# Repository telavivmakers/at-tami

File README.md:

ATtami עָלֵקדוּאִינו
=================

fork of littlewire AVR based Vusb dev board and various other efforts around the ATtiny85 <br>
more at [docs.telavivmakers.space/attami](https://docs.telavivmakers.space/attami)<br>

Schematics
===

board layout
===

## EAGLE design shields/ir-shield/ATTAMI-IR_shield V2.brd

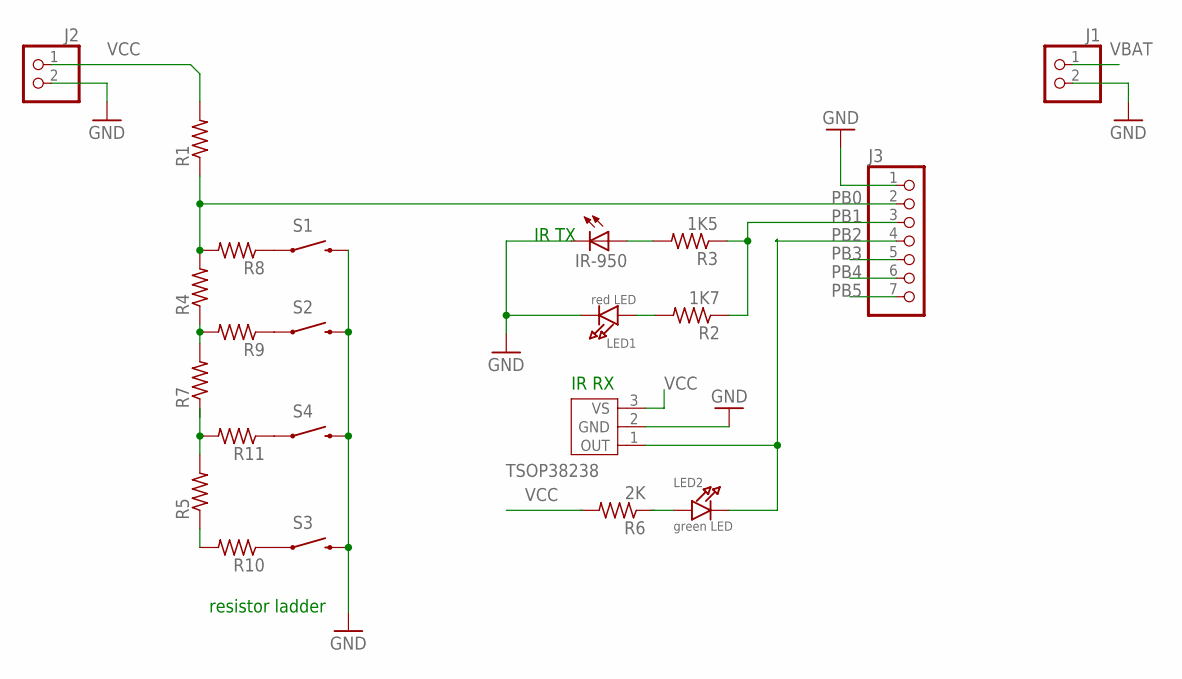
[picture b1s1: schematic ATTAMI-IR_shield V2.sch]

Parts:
IR-950: LEDIRL80A; IRL80A
J1, J2: HEADER-1X2ROUND; 1X02_ROUND
J3: HEADER-1X7ROUND; 1X07_ROUND
LED1: red LED; CHIPLED_0805
LED2: green LED; CHIPLED_0805
R1, R4, R5, R7, R8, R9, R10, R11: R-US_M0805; M0805
R2: 1K7; M0805
R3: 1K5; M0805
R6: 2K; M0805
S1, S2, S3, S4: SWITCH-MOMENTARY-2-SMD-1101NE; TACTILE-SWITCH-1101NE
TSOP38238: TSOP382; 3P-2.54-4.8X5X6.95H

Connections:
GND: IR-950.K (C), J1.2, J2.2, J3.1, LED1.C, S1.P$2 (2), S2.P$2 (2), S3.P$2 (2), S4.P$2 (2), TSOP38238.2 (GND)
unnamed: R9.1, S2.P$1 (1)
unnamed: R8.1, S1.P$1 (1)
unnamed: R10.1, S3.P$1 (1)
unnamed: LED1.A, R2.2
unnamed: R5.2, R11.2
unnamed: R4.1, R7.2, R9.2
unnamed: R5.1, R10.2
unnamed: IR-950.A, R3.2
unnamed: R11.1, S4.P$1 (1)
PB0: J3.2, R1.1, R4.2, R8.2
PB1: J3.3, R2.1, R3.1
PB2: J3.4, LED2.C, TSOP38238.1 (OUT)
PB3: J3.5
PB4: J3.6
PB5: J3.7
VBAT: J1.1
VCC: J2.1, R1.2, TSOP38238.3 (VS)

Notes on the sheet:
resistor ladder
IR TX
IR RX

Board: 2 copper layers, 22 parts (0 on the bottom side), 14 nets, no tracks yet.

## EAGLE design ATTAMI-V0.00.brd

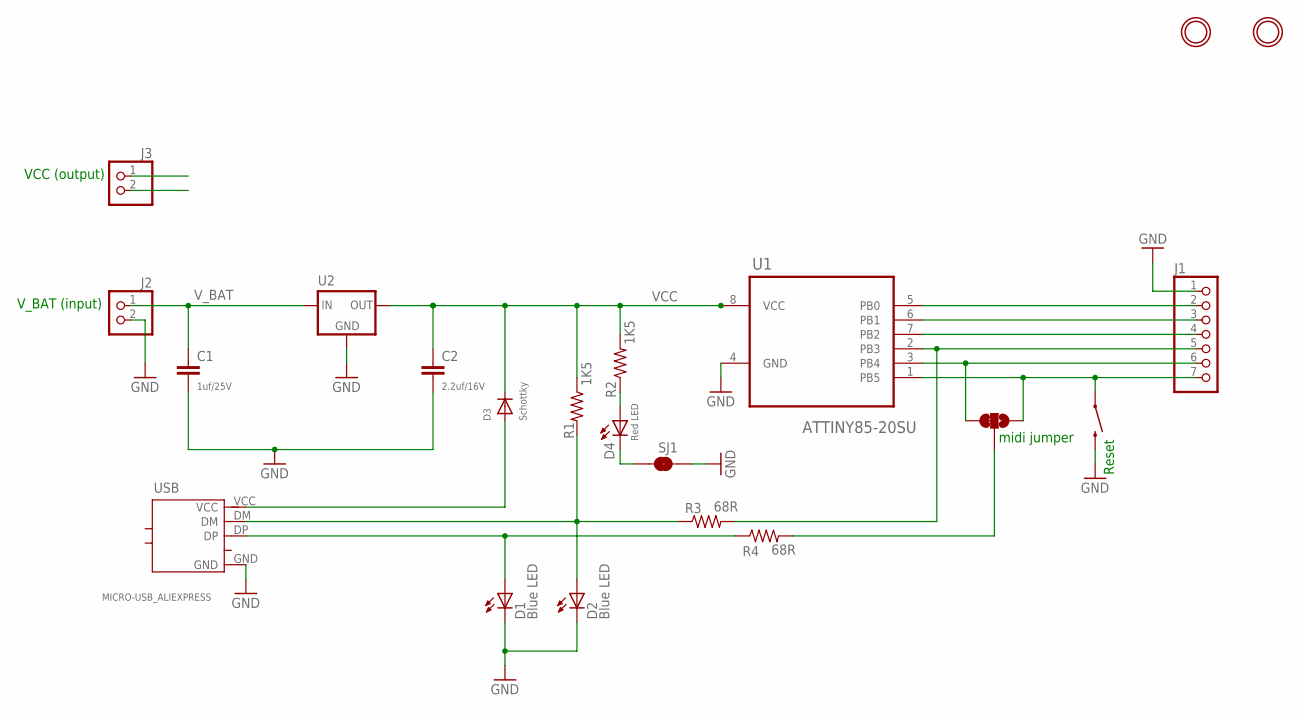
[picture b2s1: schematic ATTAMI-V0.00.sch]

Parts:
C1: 1uf/25V; 0805
C2: 2.2uf/16V; 0805
D1, D2: Blue LED; LED-805
D3: Schottky; SOD-323
D4: Red LED; LED-805
J1: HEADER-1X7ROUND; 1X07_ROUND
J2, J3: HEADER-1X2ROUND; 1X02_ROUND
MIDI: JUMPER-PAD-3-2OF3_NC_BY_TRACE_SMALL; PAD-JUMPER-3-2OF3_NC_BY_TRACE_YES_SILK_FULL_BOX
R1, R2: 1K5; 0805
R3, R4: 68R; 0805
S1: SWITCH-MOMENTARY-2-SMD-1101NE; TACTILE-SWITCH-1101NE
SJ1: JUMPER-PAD-2-NC_BY_TRACE; PAD-JUMPER-2-NC_BY_TRACE_YES_SILK
U1: ATTINY85-20SU; SOIC127P798X216-8N
U2: XXX1117SOT-232; SOT-223
U$1, U$2: MOUNTINGHOLE2.0; MOUNTINGHOLE_2.0_PLATED
USB: MICRO-USB_ALIEXPRESS; USB-MICRO-ALIEXPRESS

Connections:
GND: C1.2, C2.2, D1.C, D2.C, J1.1, J2.2, J3.2, S1.P$2 (2), SJ1.1, U1.4 (GND), U2.1 (GND), USB.GND
unnamed: MIDI.2, R4.2
unnamed: D1.A, R4.1, USB.DP
unnamed: D2.A, R1.2, R3.1, USB.DM
unnamed: D4.A, R2.1
unnamed: D4.C, SJ1.2
PB0: J1.2, U1.5 (PB0)
PB1: J1.3, U1.6 (PB1)
PB2: J1.4, U1.7 (PB2)
PB3: J1.5, R3.2, U1.2 (PB3)
PB4: J1.6, MIDI.3, U1.3 (PB4)
PB5: J1.7, MIDI.1, S1.P$1 (1), U1.1 (PB5)
V-BUS: D3.AQ (A), USB.VCC
VCC: C2.1, D3.CQ (C), J3.1, R1.1, R2.2, U1.8 (VCC), U2.2 (OUT), U2.4 (OUT)
V_BAT: C1.1, J2.1, U2.3 (IN)

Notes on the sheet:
VCC (output)
V_BAT (input)
Reset
midi jumper

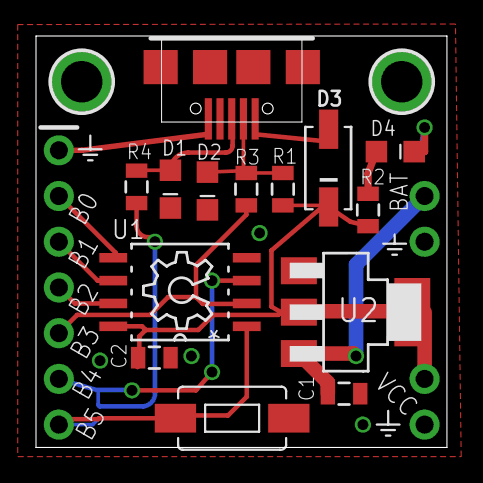
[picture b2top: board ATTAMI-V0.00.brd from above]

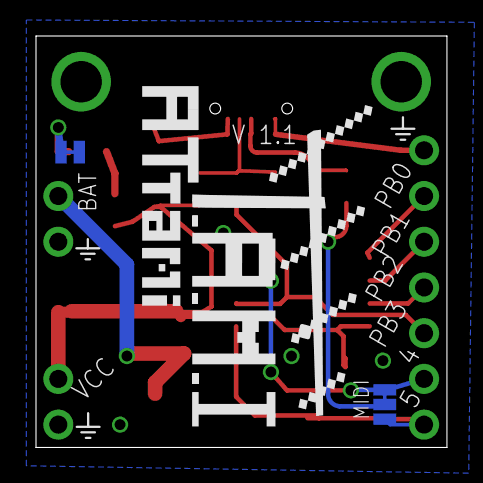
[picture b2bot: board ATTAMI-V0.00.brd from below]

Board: 2 copper layers, 22.8 x 22.9 mm, 22 parts (2 on the bottom side), 15 nets.

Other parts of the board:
U$3: OSHW_6X150_NOTEXT

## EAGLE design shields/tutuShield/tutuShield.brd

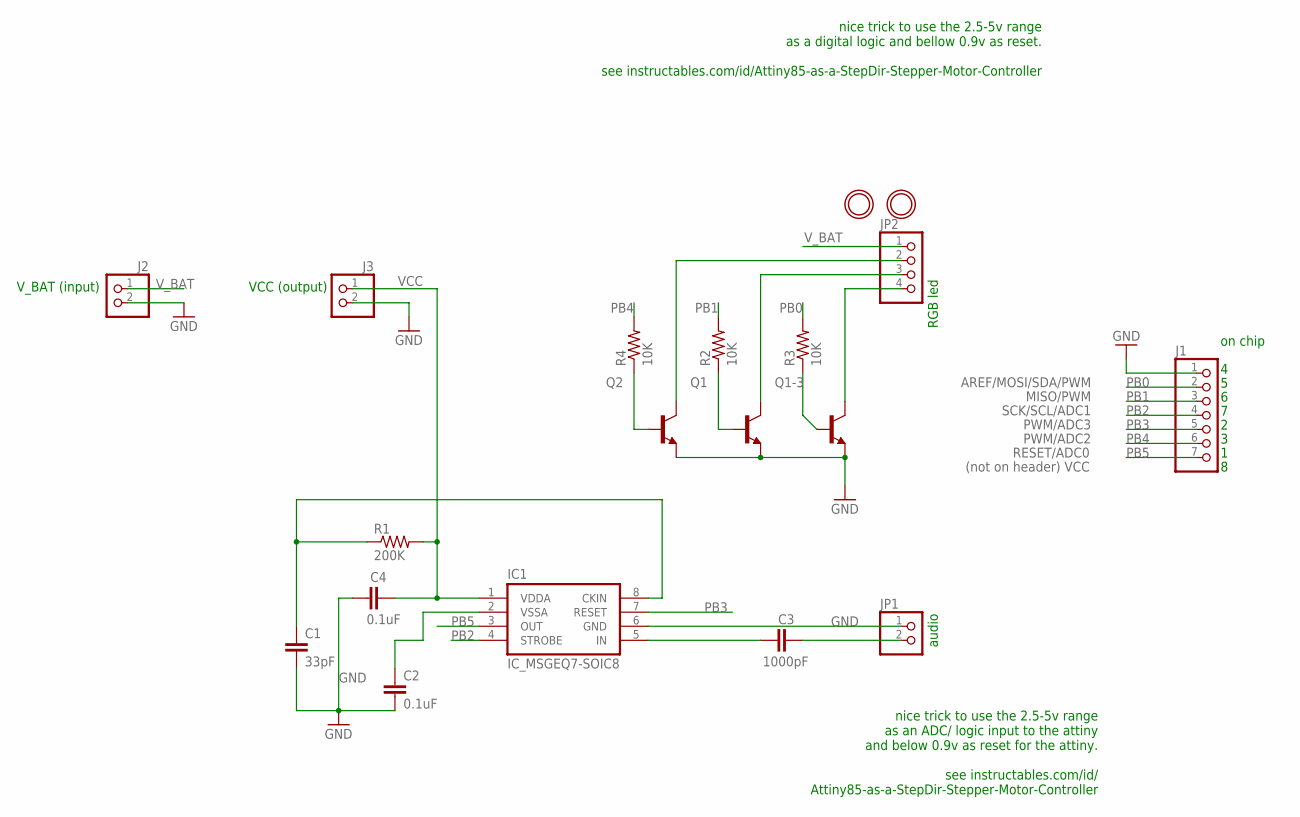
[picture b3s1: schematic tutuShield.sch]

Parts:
C1: 33pF; 0805
C2, C4: 0.1uF; 0805
C3: 1000pF; 0805
IC1: IC_MSGEQ7-SOIC8; SOIC-8
J1: HEADER-1X7ROUND; 1X07_ROUND
J2, J3: HEADER-1X2ROUND; 1X02_ROUND
JP1: HEADER-1X2ROUND; 1X02_ROUND
JP2: HEADER-1X4ROUND; 1X04_ROUND
Q1, Q1-3, Q2: TRANSISTOR_BJT_NPN-SOT-23-BEC; SOT-23
R1: 200K; 0805
R2, R3, R4: 10K; 0805
U$1, U$2: MOUNTINGHOLE2.0; MOUNTINGHOLE_2.0_PLATED

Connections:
CKIN: C1.1, IC1.8 (CKIN), R1.1
GND: C1.2, C2.2, C4.1, IC1.6 (GND), J1.1, J2.2, J3.2, JP1.1, Q1.2 (E), Q1-3.2 (E), Q2.2 (E)
IN: C3.1, IC1.5 (IN)
unnamed: C3.2, JP1.2
unnamed: Q1-3.1 (B), R3.1
unnamed: JP2.2, Q2.3 (C)
unnamed: C2.1, IC1.2 (VSSA)
unnamed: Q1.1 (B), R2.1
unnamed: Q2.1 (B), R4.1
unnamed: JP2.4, Q1-3.3 (C)
unnamed: JP2.3, Q1.3 (C)
PB0: J1.2, R3.2
PB1: J1.3, R2.2
PB2: IC1.4 (STROBE), J1.4
PB3: IC1.7 (RESET), J1.5
PB4: J1.6, R4.2
PB5: IC1.3 (OUT), J1.7
VCC: C4.2, IC1.1 (VDDA), J3.1, R1.2
V_BAT: J2.1, JP2.1

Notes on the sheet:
VCC (output)
V_BAT (input)
RESET/ADC0
PWM/ADC3
SCK/SCL/ADC1
PWM/ADC2
MISO/PWM
AREF/MOSI/SDA/PWM
on chip 4 5 6 7 2 3 1 8
(not on header) VCC
nice trick to use the 2.5-5v range as a digital logic and bellow 0.9v as reset. see instructables.com/id/Attiny85-as-a-StepDir-Stepper-Motor-Controller
nice trick to use the 2.5-5v range as an ADC/ logic input to the attiny and below 0.9v as reset for the attiny. see instructables.com/id/ Attiny85-as-a-StepDir-Stepper-Motor-Controller
audio
RGB led

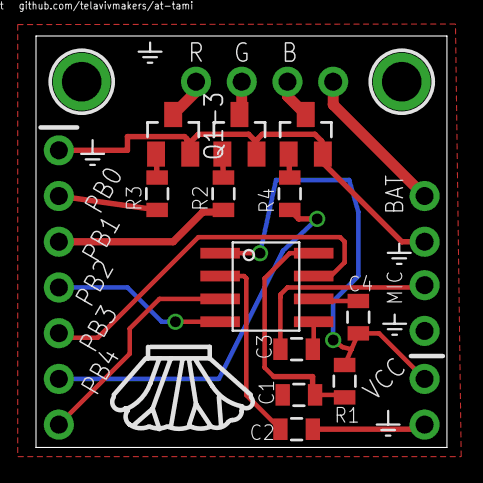
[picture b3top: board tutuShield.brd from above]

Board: 2 copper layers, 22.8 x 22.9 mm, 19 parts (0 on the bottom side), 19 nets.

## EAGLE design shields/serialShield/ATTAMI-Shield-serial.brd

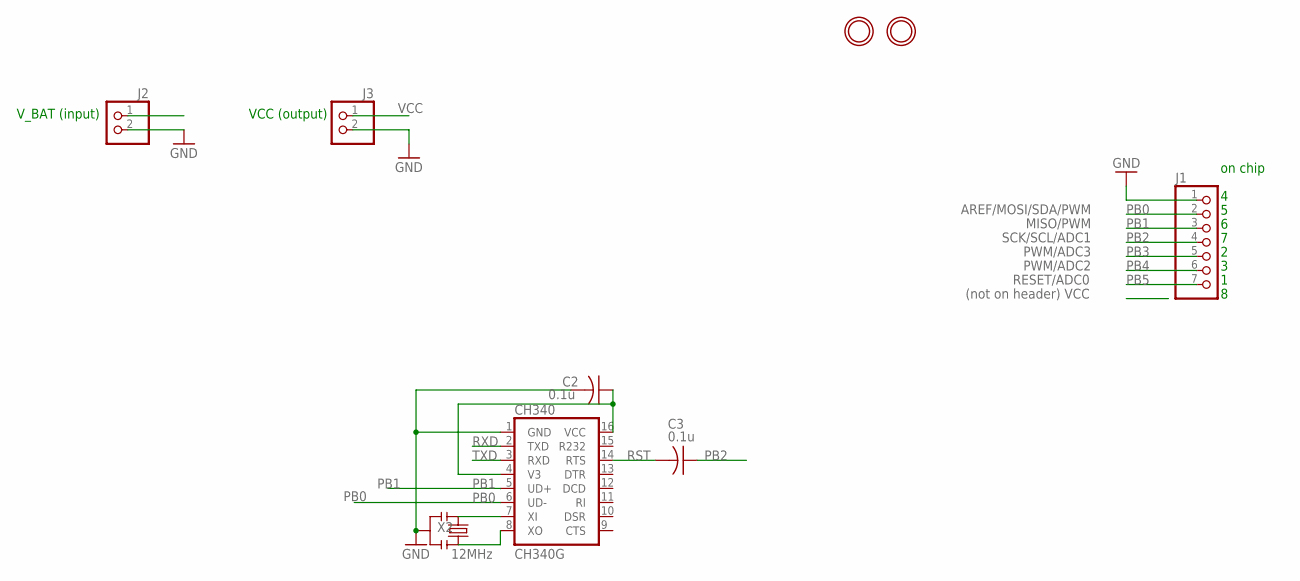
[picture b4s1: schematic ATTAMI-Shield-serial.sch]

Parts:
C2, C3: 0.1u; C0603
CH340: CH340G; SO16
J1: HEADER-1X7ROUND; 1X07_ROUND
J2, J3: HEADER-1X2ROUND; 1X02_ROUND
U$1, U$2: MOUNTINGHOLE2.0; MOUNTINGHOLE_2.0_PLATED
X2: 12MHz; RESONATOR-SMD

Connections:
GND: C2.2, CH340.1 (GND), J1.1, J2.2, J3.2, X2.2
unnamed: CH340.7 (XI), X2.1
unnamed: CH340.8 (XO), X2.3
PB0: CH340.6 (UD-), J1.2
PB1: CH340.5 (UD+), J1.3
PB2: C3.1, J1.4
PB3: J1.5
PB4: J1.6
PB5: J1.7
RST: C3.2, CH340.14 (RTS)
RXD: CH340.2 (TXD)
TXD: CH340.3 (RXD)
VCC: C2.1, CH340.4 (V3), CH340.16 (VCC), J3.1

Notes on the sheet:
VCC (output)
V_BAT (input)
RESET/ADC0
PWM/ADC3
SCK/SCL/ADC1
PWM/ADC2
MISO/PWM
AREF/MOSI/SDA/PWM
on chip 4 5 6 7 2 3 1 8
(not on header) VCC

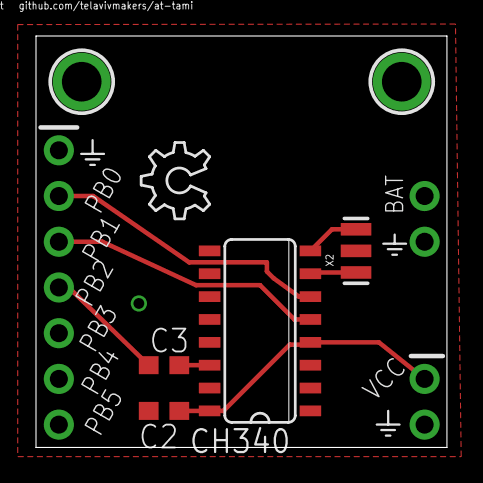
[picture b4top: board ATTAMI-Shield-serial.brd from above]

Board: 2 copper layers, 22.8 x 22.9 mm, 10 parts (0 on the bottom side), 8 nets.

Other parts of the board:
U$3: OSHW_6X150_NOTEXT

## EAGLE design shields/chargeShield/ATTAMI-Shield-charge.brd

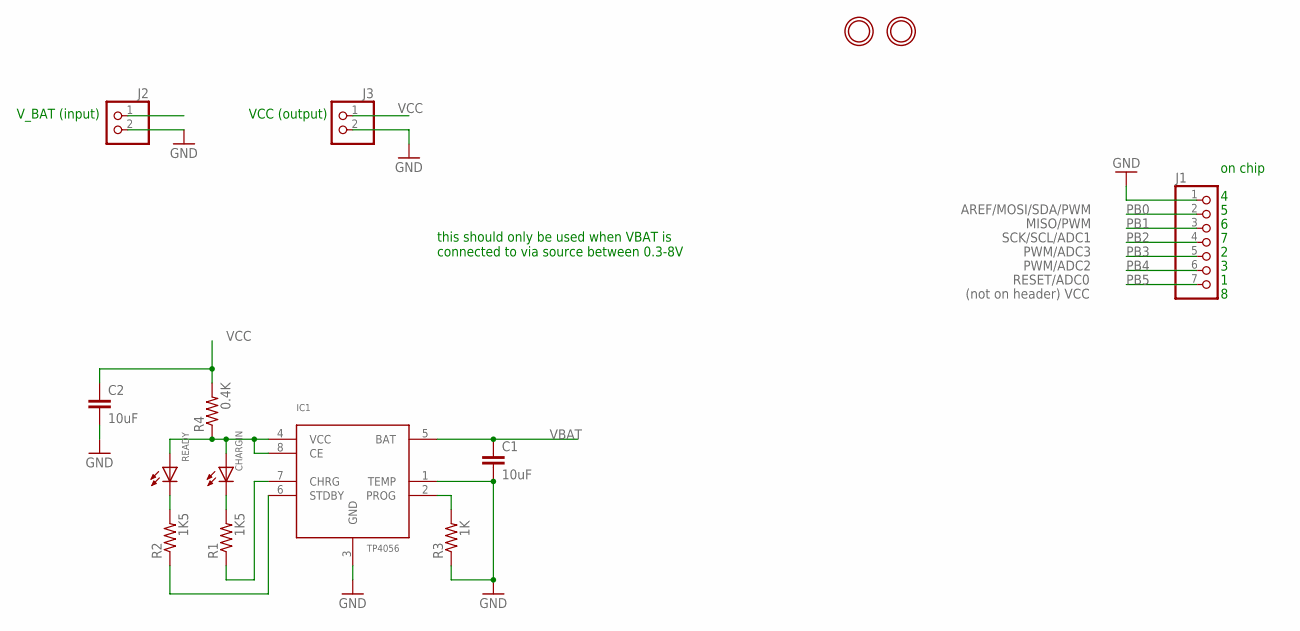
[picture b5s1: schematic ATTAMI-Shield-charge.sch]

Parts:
C1, C2: 10uF; 0805
CHARGIN: LED-0805; LED-805
IC1: TP4056; SOP-8
J1: HEADER-1X7ROUND; 1X07_ROUND
J2, J3: HEADER-1X2ROUND; 1X02_ROUND
R1, R2: 1K5; 0805
R3: 1K; 0805
R4: 0.4K; 0805
READY: LED-0805; LED-805
U$1, U$2: MOUNTINGHOLE2.0; MOUNTINGHOLE_2.0_PLATED

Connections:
$02: CHARGIN.A, IC1.4 (VCC), IC1.8 (CE), R4.1, READY.A
GND: C1.2, C2.2, IC1.1 (TEMP), IC1.3 (GND), J1.1, J2.2, J3.2, R3.1
unnamed: IC1.2 (PROG), R3.2
unnamed: R2.2, READY.C
unnamed: CHARGIN.C, R1.2
unnamed: IC1.6 (STDBY), R2.1
unnamed: IC1.7 (CHRG), R1.1
PB0: J1.2
PB1: J1.3
PB2: J1.4
PB3: J1.5
PB4: J1.6
PB5: J1.7
VBAT: C1.1, IC1.5 (BAT), J2.1
VCC: C2.1, J3.1, R4.2

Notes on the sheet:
VCC (output)
V_BAT (input)
RESET/ADC0
PWM/ADC3
SCK/SCL/ADC1
PWM/ADC2
MISO/PWM
AREF/MOSI/SDA/PWM
on chip 4 5 6 7 2 3 1 8
(not on header) VCC
this should only be used when VBAT is connected to via source between 0.3-8V

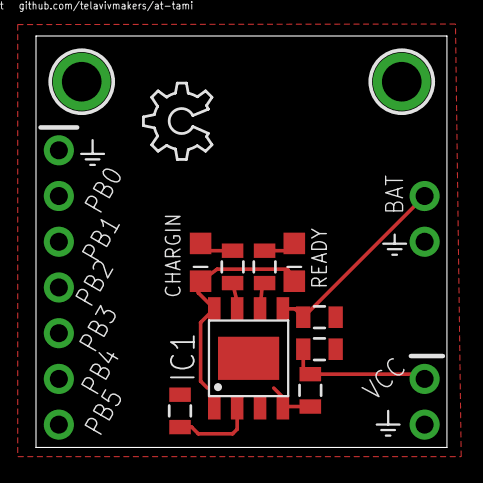
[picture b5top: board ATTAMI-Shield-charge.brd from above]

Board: 2 copper layers, 22.8 x 22.9 mm, 15 parts (0 on the bottom side), 9 nets.

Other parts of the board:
U$3: OSHW_6X150_NOTEXT

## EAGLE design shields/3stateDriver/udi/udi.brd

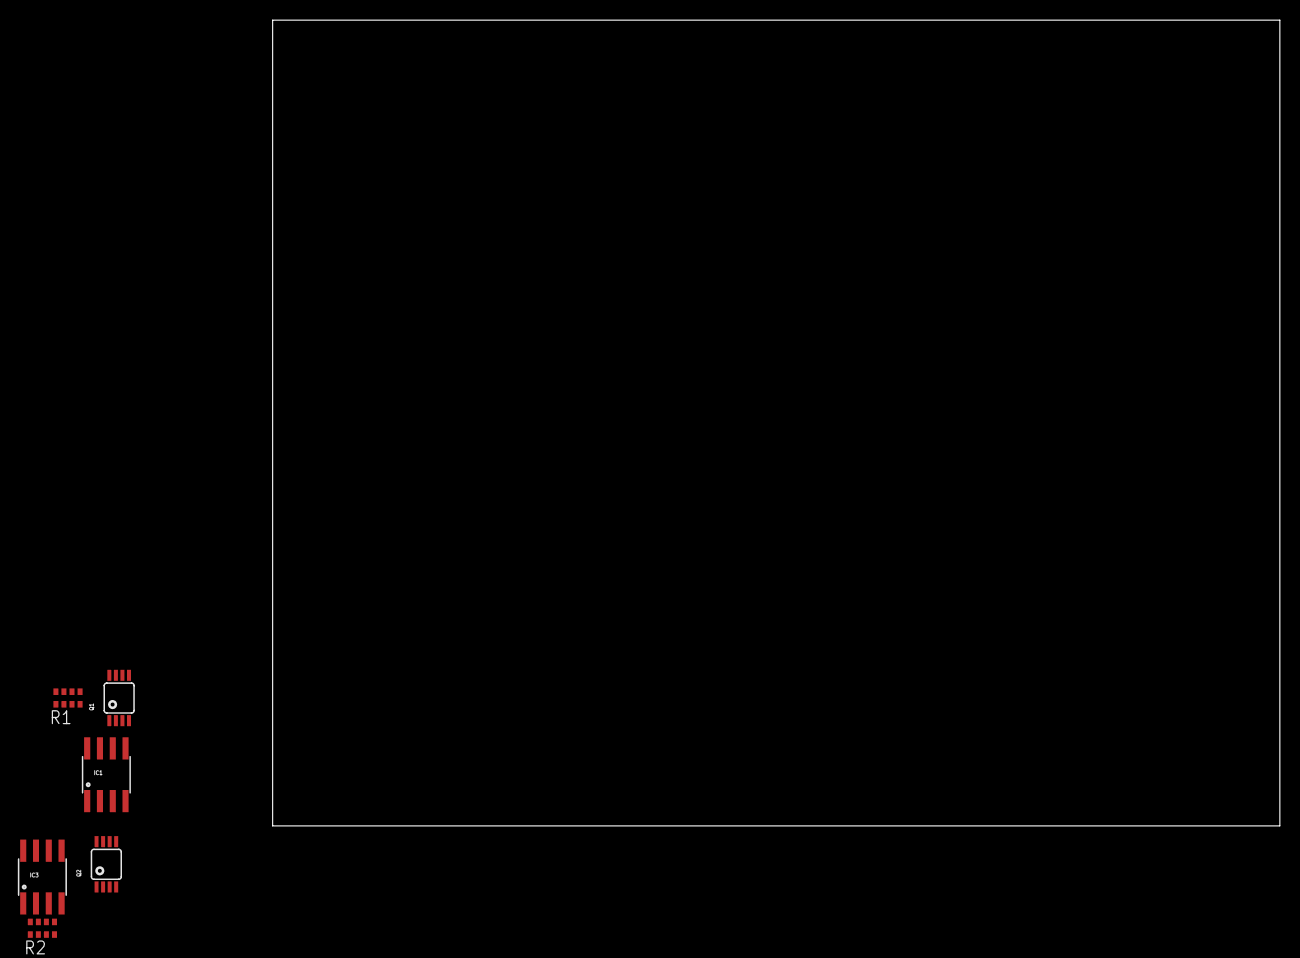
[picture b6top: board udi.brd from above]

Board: 2 copper layers, 100.0 x 80.0 mm, 6 parts (0 on the bottom side), 15 nets, no tracks yet.

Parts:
IC1, IC3: OPAMP-DUALU; SO08
Q1, Q2: MSOP8
R1, R2: 0603-ARV

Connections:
GND-ISO: Q1.1, Q2.1, R1.4, R2.4
unnamed: IC1.1, R1.1
unnamed: Q1.4, R1.2, R1.8
unnamed: IC1.3, IC1.5, R1.3, R1.5
unnamed: Q1.5, Q1.6, R1.7
unnamed: Q1.3, Q1.7, Q1.8
unnamed: IC1.7, Q1.2
unnamed: IC3.1, R2.1
unnamed: Q2.4, R2.2, R2.8
unnamed: IC1.6, IC3.5
unnamed: Q2.5, Q2.6, R2.7
unnamed: Q2.3, Q2.7, Q2.8
unnamed: IC3.7, Q2.2
V+: IC1.8, IC3.8
V-: IC1.4, IC3.4

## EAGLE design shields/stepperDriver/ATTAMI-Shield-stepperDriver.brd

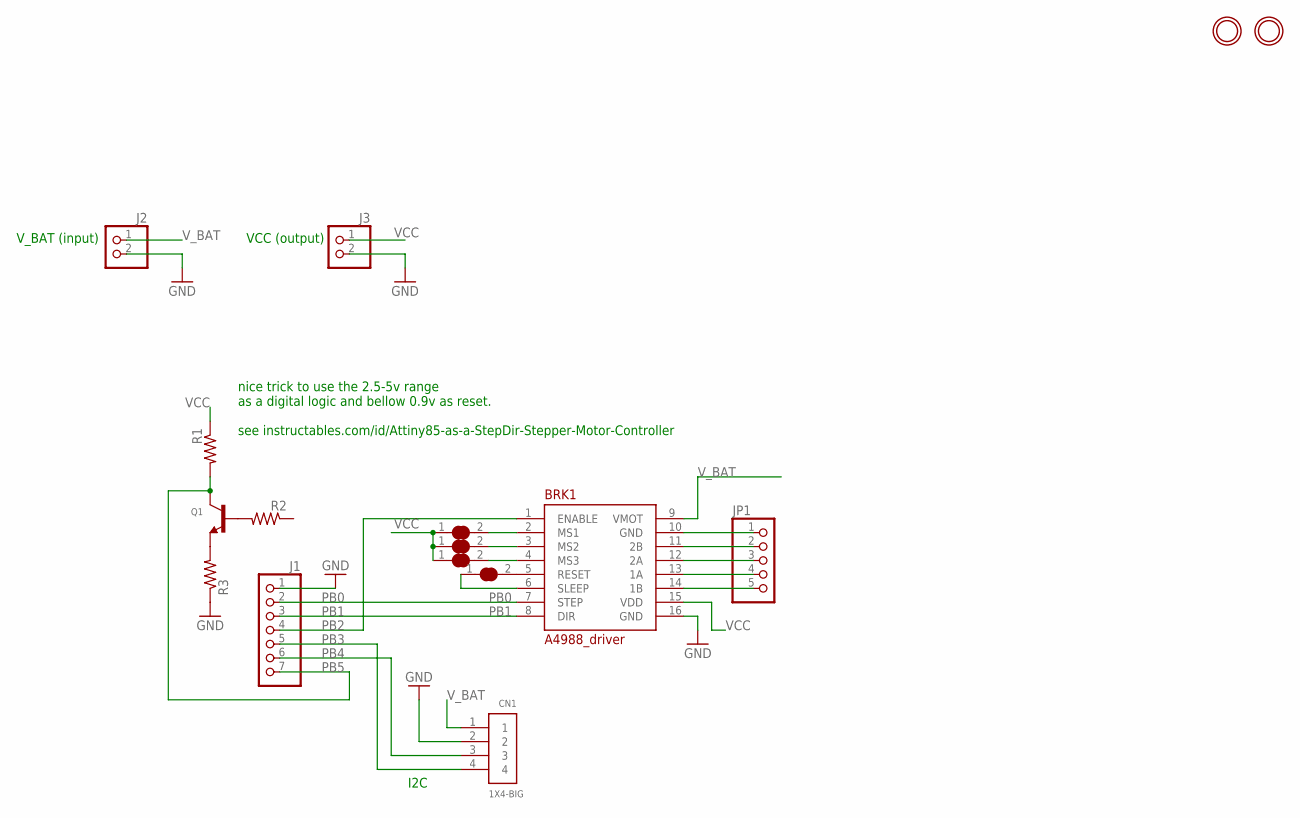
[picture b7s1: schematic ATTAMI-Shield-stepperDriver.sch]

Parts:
BRK1: A4988_driver; DIL16
CN1: 1X4-BIG; 1X04-BIG
J1: HEADER-1X7ROUND; 1X07_ROUND
J2, J3: HEADER-1X2ROUND; 1X02_ROUND
JP1: HEADER-1X5; 1X05_OVAL
Q1: TRANSISTOR_NPNWAVE; SOT23-W
R1, R2, R3: R-US_R0805; R0805
SJ1, SJ2, SJ3, SJ4: SOLDERJUMPER_CLOSED; SOLDERJUMPER_CLOSEDWIRE
U$1, U$2: MOUNTINGHOLE2.0; MOUNTINGHOLE_2.0_PLATED

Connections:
GND: BRK1.10 (GND), BRK1.16 (GND), CN1.2, J1.1, J2.2, J3.2, JP1.1, R3.1
unnamed: BRK1.5 (RESET), SJ4.2
unnamed: BRK1.11 (2B), JP1.2
unnamed: Q1.2 (E), R3.2
unnamed: Q1.1 (B), R2.2
unnamed: BRK1.12 (2A), JP1.3
unnamed: BRK1.13 (1A), JP1.4
unnamed: BRK1.14 (1B), JP1.5
unnamed: BRK1.6 (SLEEP), SJ4.1
unnamed: BRK1.2 (MS1), SJ3.2
unnamed: BRK1.3 (MS2), SJ2.2
unnamed: BRK1.4 (MS3), SJ1.2
PB0: BRK1.7 (STEP), J1.2
PB1: BRK1.8 (DIR), J1.3
PB2: BRK1.1 (ENABLE), J1.4
PB3: CN1.4, J1.5
PB4: CN1.3, J1.6
PB5: J1.7, Q1.3 (C), R1.2
VCC: BRK1.15 (VDD), J3.1, R1.1, SJ1.1, SJ2.1, SJ3.1
V_BAT: BRK1.9 (VMOT), CN1.1, J2.1

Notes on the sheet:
VCC (output)
V_BAT (input)
nice trick to use the 2.5-5v range as a digital logic and bellow 0.9v as reset. see instructables.com/id/Attiny85-as-a-StepDir-Stepper-Motor-Controller
I2C

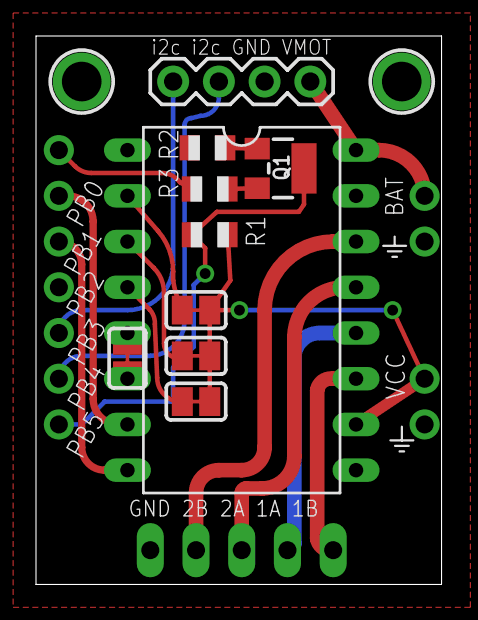
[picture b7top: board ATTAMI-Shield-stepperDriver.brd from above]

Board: 2 copper layers, 22.5 x 30.5 mm, 16 parts (0 on the bottom side), 20 nets.

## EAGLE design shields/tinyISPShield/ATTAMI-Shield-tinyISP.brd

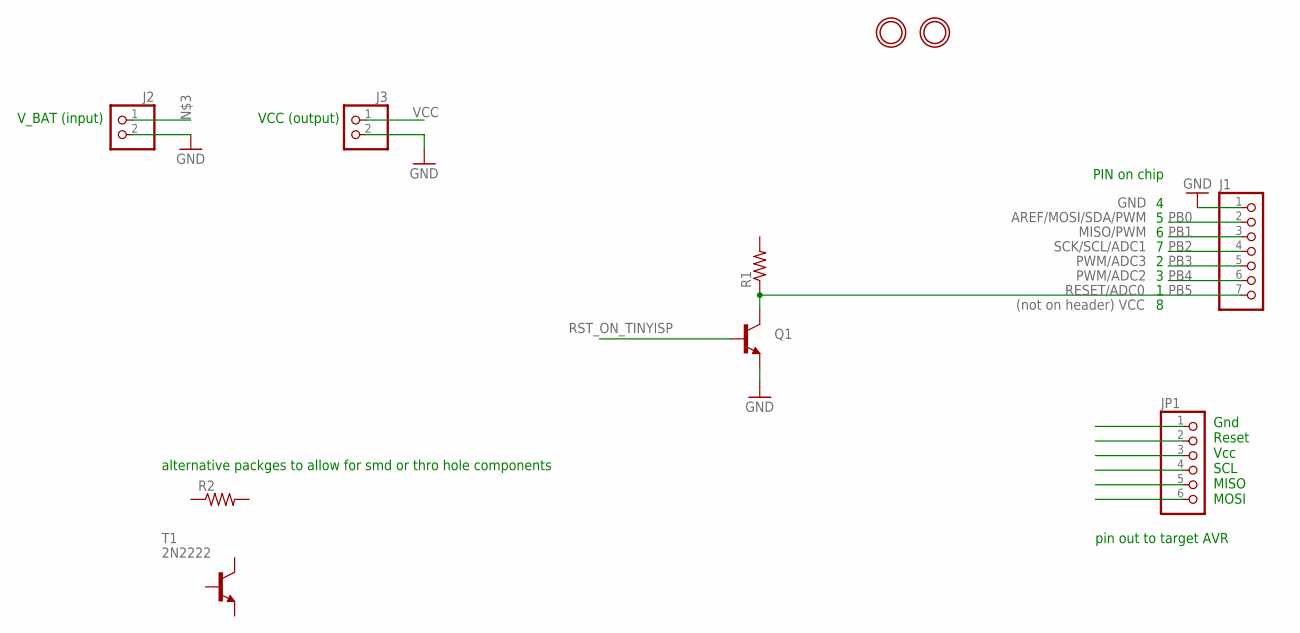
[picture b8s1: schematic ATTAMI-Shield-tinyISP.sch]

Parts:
J1: HEADER-1X7ROUND; 1X07_ROUND
J2, J3: HEADER-1X2ROUND; 1X02_ROUND
JP1: HEADER-1X6ROUND; 1X06_ROUND
Q1: TRANSISTOR_NPNSOT23; SOT23
R1: RESISTOR0805-RES; 0805
R2: RESISTORAXIAL-0.3; AXIAL-0.3
T1: 2N2222; TO92-EBC-OVAL
U$1, U$2: MOUNTINGHOLE2.0; MOUNTINGHOLE_2.0_PLATED

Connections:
GND: J1.1, J2.2, J3.2, Q1.2 (E)
PB0: J1.2
PB1: J1.3
PB2: J1.4
PB3: J1.5
PB4: J1.6
PB5: J1.7, Q1.3 (C), R1.1
RST_ON_TINYISP: Q1.1 (B)
VCC: J3.1

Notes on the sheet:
VCC (output)
V_BAT (input)
RESET/ADC0
PWM/ADC3
SCK/SCL/ADC1
PWM/ADC2
MISO/PWM
AREF/MOSI/SDA/PWM
Gnd Reset Vcc SCL MISO MOSI
pin out to target AVR
PIN on chip 4 5 6 7 2 3 1 8
(not on header) VCC
GND
alternative packges to allow for smd or thro hole components

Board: 2 copper layers, 11 parts (0 on the bottom side), 2 nets, no tracks yet.

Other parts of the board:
U$3: OSHW_6X150_NOTEXT

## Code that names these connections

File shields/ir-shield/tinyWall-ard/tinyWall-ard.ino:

// ATMEL ATTINY85 running @ 8MHz / ARDUINO **Zvi Schneider 12-May-2014**
//           		 +----\/---+
//  ADC0,  PB5, 	1|*           |8	VCC
//  ADC3,  PB3,	2|             |7	PB2,  ADC1
//  ADC2,  PB4,	3|             |6	PB1,
//  GND       	4|             |5	PB0,
//              		 +---------+
// http://telavivmakers.org/index.php/TinyWall
// https://github.com/telavivmakers/at-tami/tree/master/shields/ir-shield

#define my_milisec  76 // 76 interrupts equal 1 mili-sec (approximatly)
#define interval  100 //100 mili-sec interval between repetetive code transmitions
volatile long interrups_counter = 0;
byte virtual_wall = B10100010; // ROOMAs virtual wall code
int one_milisec = my_milisec;
int three_milisec = my_milisec * 3;

ISR (TIM0_COMPA_vect) { // interrupt service routine
  interrups_counter +=1;
}

void setup(){
  TCNT0 = 0; //initialize timer0 registers
  TCCR0A=0;
  TCCR0B=0;
  TCCR0A |=(1<<COM0A0); //Timer0 in toggle mode (Table 11-2)
  TCCR0A |=(1<<WGM01); //Timer0 in CTC mode (Table 11.5)
  TCCR0B |= (1 << CS00);// Prescaler (table 11.6, no prescaling)
  OCR0A=105-1; //CTC Compare value. with 8MHz clock and no prescaling this value will give interrupt every 13.125 micro-sec
  TIMSK |= 1<<OCIE0A; //enable timer0 OCR0A interrups
  SREG |= B10000000; //enable interrups
}

void loop(){
  while (interrups_counter < my_milisec*interval){ //wait interval miliseconds
  }
  interrups_counter = 0;
  xmitbyte(virtual_wall); //send one byte command to the ROOMBA
}

void xmitbyte(byte xmitdata){
  int i;
  int mark;
  int space;
  byte shift_one = B10000000;
  for (i = 0; i < 8; i++){
    if (xmitdata & shift_one){
      mark = three_milisec;
      space = one_milisec;
    }
    else {
      mark = one_milisec;
      space = three_milisec;
    }
    pinMode(PB0, OUTPUT); // mark, transmit IR pulses
    while (interrups_counter < mark){
    }
    interrups_counter = 0;
    pinMode(PB0, INPUT); // space, do not transmit IR pulses
    while (interrups_counter < space){
    }
    interrups_counter = 0;
    shift_one = shift_one >> 1;
  }
}

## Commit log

2014-03-22 eagle board layout
2014-03-26 fixed stuff
2014-04-08 fixed unrouted wires
2014-05-08 changed name and updated to rev4
2014-05-08 changed name and updated to rev04
2014-05-09 ver05 friday session
2014-05-15 ver07
    http://i.imgur.com/BFdtqUi.jpg
2014-05-15 ver07
    https://dl.dropboxusercontent.com/u/6430706/ShareX/2014/05/TAMI-ATTINY-V07.pdf
2014-05-25 ver08
    [zvi] switched the LDO to MIC5225. also changed some capacitors.
2014-05-25 ver 09
    [zvi] changed the schematics. MIC5205 is in together with its capacitor C3.
    The MIC5205 has two drawbacks:
    a. No guaranteed behavior for Vin < 5.5 V.
    b. No guaranteed behavior regarding reverse leakage.
    For applications with external supply greater than 5.5V there is no problem.
    We will have to test the reverse current issue when operating on USB 5V without external supply.
2014-06-02 ver 12
2014-06-04 ver 15b
2014-06-04 ver 15b
    this could be printed....
2014-06-04 ver 15c
    curved and fixed overlaps
    used DRU rules by OSHpark
    https://oshpark.com/guidelines
2014-06-04 ver 15c
    no change
2014-06-07 15b-04
    almost done
2014-06-07 15b-03
2014-06-12 ver 15b05
    now the polygon back silkscreen logo placed correctly, ready for panalizing(!)
2014-06-12 15b06
    because of sobbing of online gerber checker
    https://www.freedfm.com/freedfm/0022376203858107/results/summary2.htm
    - enlarge fonts on silkscreen to min 5mil
    - removed some redundant polygons from bottom silk
2014-06-16 Create ATTAMI-Shield-template.sch
    template for shields
2014-06-16 Create ATTAMI-Shield-template.brd
    template for sheilds
2014-06-16 ver 16
    now with stock DOC_frame
2014-06-16 Create TAMI-oshpark-gerb274x.cam
    used for exporting ATtami for valid OSHpark gerber files
    its based on the sparkfun cam gerb274x file, but
    added outline output (.GKO)
    added layer 25 (tNames) to top silkscreen (.GTO)
    added layer 26 (bNames) to bottom silkscreen (.GBO)
2014-06-16 Delete Little-Wire.J+N.pro
    this is historical, we moved to a fresh design
    thanks littleWire for showing us the way
2014-06-16 reaplced pic with ver16
2014-07-01 ver 17
    changed the USB connector to the "official" package
    MOLEX - 47346-0001 - MICRO USB TYPE B
2014-07-01 ver 17
    changed usb connector
2014-08-29 sent to FAB
    geekcon edition, with coincell
2014-08-29 template for v17
2014-08-31 Update README.md
    changed baord to v17 geekcon edition
2014-09-07 fix floating pin
    major error in voltage regualtor (U1). enable pin was not connected to
    VBAT in GKx batch :(.
2014-09-07 expanded microusb pads
    also add OSHW logo
    and removed some drawings
2014-09-07 silkscreen
    added slinkscreen to pads on the bottom
    remove tiny text from TAMI logo
2014-09-07 added hebrew slang, will it work?
2014-09-07 updated pic to ver17b
    https://github.com/telavivmakers/at-tami/commit/445718143124147e8c1c812b3e7fddc0d333db01
2014-09-08 seocnd batch to fab
    zv additions
    Added + and gnd marking near the coin-cell legs on bottom side of the
    PCB.
    Made some legend changing on the schematic.
2014-10-02 ATTami version 0.00
    PB5 connected,
    Added version # on bnames layer
    disconnected usb shield from ground
2014-10-16 changed pic to rev0
2014-10-28 same shield, with added mounting holes and better naming based on ver 0.00
    based on attami ver 0.00
    https://github.com/telavivmakers/at-tami/commit/00271a633f93de088d04ac549667f0e04d0c47cf#diff-2c24cc5344d8d061ae0f0b1c47d7ba8a
2014-10-28 ignore temp eagle files
2014-10-28 servo shield - new
    also added names and labels on wires
2014-10-28 flipped servo power pins
2014-11-05 servo shield
2014-11-05 servi inverter
2014-11-06 servo shield-no invert :(
2014-11-24 midnight edition, 1x2 layout
    taking space of two ATTami (1800x900 mil) .
    leaving much place for silkscreen.
    power on the right, servos on the left
    no VCC pins on shield.
    bottom copper plate is no longer ground, its now V_BAT.
2014-11-24 rough layout change
    switched position of servos for better layout
2014-11-25 folders
2014-11-25 cleaned template shield
2014-11-25 WIP
    basing on http://elm-chan.org/works/sd8p/report.html
    | what cap and inductor to use?
2014-11-26 changes to cap and inductor
2014-11-26 V_BAT connect to charging circuit
2014-11-26 added pdf
2014-11-26 moved pdf of sounday shield
2014-11-30 removed unused layers from eagle project
2014-11-30 vector fonts, text change
2014-12-05 new tami logo
    using svg2poly.ulp
2014-12-07 more work on generic shield
    also added an SVG with TAMI logo
2014-12-11 a shield for the pololu stepper driver, basic idea of schema and layout
    the pinout of the eagle part is a total mess. need to make my own.
    notice the PB5/RESET pin trick
2014-12-14 added ATtami eagle part library
2014-12-14 cont work on stepper shield
    mostly done, could work if we agree on V_BAT to 12V
2014-12-15 updtae A4988 lib part
2014-12-15 choose eagle files
2014-12-16 addded 4pin header for 12+ and I2C, not routed
2014-12-16 fix switched pins in stepper lib
    1A <-> 1B
2014-12-16 updated wiring, needs review
2014-12-16 added layout png
2014-12-16 remove project file
2014-12-16 added schema pdf
2014-12-28 ccc working on legend
2014-12-29 plotter
2015-01-01 added nice attami logo
2015-01-02 removed unuised ID pin from micro usb connector
2015-01-02 added attiny85 devices
    from Atmel_By_element14_Batch_1-00.lbr via farnel
2015-01-02 moved all parts to ATtami lib, trimmed it
2015-01-03 updated layout
    including re-routing the EN-VIN connection on U1 and removing a few
    routes that allows for this design to work as a one layer board with a
    bit of work.
2015-01-03 updated logo for the ATtami
2015-01-04 small layout change
2015-01-04 re introduced the vias under the regulator
2015-01-04 moved ATtami logo to the shield example
2015-01-04 add 1x4 and 1x6 headers to the library
2015-01-04 added pin number on breakout header
2015-01-04 new shield (in progress)
2015-01-08 changes in trace width (8mil) and fine tune the aliexpress microusb packge
2015-01-08 new design with added AMS1117 voltage regulator
    with library reflecting the part
2015-01-10 start tutushield
2015-01-10 added MSGEQ7 to lib
2015-01-10 added msgeq7 + capacitor & resistors
2015-01-10 didn't save last time :\
2015-01-11 small rewire
2015-01-11 updated shield tamplete to only use ATtami lib parts
2015-01-11 layout fixing and pdf
2015-01-12 charge shield
2015-01-16 new serial shield
    around CH340G (CH340) ic
2015-01-16 simplfy
    this is a driver design we need a barebone onn with High Speed
    Optoisolator SOIC 16 , 60V 4A.
2015-01-16 added the pb5 as digitall/reset pin thing
    also text comments
2015-01-16 sorry, i mixed signals
2015-01-16 a version without the PB5 trick
    it might be a bit simpler but i think its worth it to stick to
    4af68e7c457e82ac5364ccc3b228164f2045e11b
2015-01-16 routed
    without the PB5
2015-01-16 done schema
2015-01-18 fix GND and VCC airwires
2015-01-19 an attami device added to lib
2015-01-19 Moved via because of DRC rules
    Moved via next to the main chip because of DRC rules and 'ratsnest'ed it
2015-01-21 tutu vectrozied
2015-01-22 Added Gitter badge
2015-01-24 added tutu logo and BMP file
2015-01-24 fixed vcc wire bugs
2015-01-24 added tutu images and caption
2015-01-24 added elecros gerber cam job for eagle
2015-01-27 ready to ship, nice low via count
2015-01-27 final schematics and board
2015-01-28 fixed sizes of silkscreen fonts (was smaller then 32mil)
2015-01-28 added directory with current pcb house rules for eagle
2015-01-28 removed pictures from tutu shield dir
2015-01-28 cleaning
2015-01-28 gitignore now works also on subfolders
2015-01-28 gitignore eagle jobs
2015-02-12 New look for "ATTAMI_BREAKOUT_SHIELD"
2015-02-25 new looks from zvi
2015-03-03 added zif to lib
2015-03-07 rewire the npn transistors
2015-03-09 fixed pwm misshap in tutu shield
2015-03-15 3state stepperdriver added (WIP)
2015-03-15 some addition to 3state driver udi
2015-03-17 mostly lib work
2015-04-03 fixed tutushield, needs review
2015-04-03 fixed some github problems. added the jumper to allow for midi out. intgrated the 2nd voltage regulator to make it cheap again
2015-04-03 pushed the pb5 wire a bit to the cneter
2015-04-07 fixed attami.lbr , taken correct attami template from high-voltage-programmer schema
2015-04-15 hl version
2015-04-16 Added remarks
2015-04-16 Some changes of the routing
2015-04-16 replaced PDF file
2015-04-16 hopefully didnt bork everything with zvi pull req
2015-04-16 new pdf with zvi remarks
2015-04-16 fixed pesky unconnected wires in jumper,, and removed value from jumer
2015-07-22 added kicad WIP folder
2015-07-22 10mil width traces and pushed the PB5 bottom trace up
2015-07-22 added gerbmerge oldie
2015-07-22 removed kicad, need to start again
2015-07-23 updated pdf
2015-07-23 new baord ready for panelizition in win32
2015-07-23 new gerber sent to be approved by pcb house #1 for 2015
2015-07-23 fixed some airwires in the board, and new panelize
2015-07-23 Update README.md
    new pics of board
2015-07-23 a versin without the fancy LDO and SOT0232 for the X1117
2015-07-30 moved power led jumper to top layer
2015-08-03 gerbering to fab
2015-08-03 ***sent to fab***
2015-08-08 removed generated gerber, will add from email to elecrow
2015-08-19 assmbly instructions
2015-08-19 assmbly instructions risze paper
2015-08-19 2x2 layout
2015-08-19 layout chage for D4
2015-08-19 plotter stencil
2015-08-19 new schema pdf
2015-10-10 correction to bat/gnd marking on top silk, it was reversed
2015-10-15 tweaked the usb pads, sending to fab
2015-10-30 new gerber reflecting correct gnd/vcc silkscreen. also refernace to zofz 3d gerber viewr
2015-11-04 added ir shiled from zvi
2015-11-04 added tinywall code
2015-11-04 links
2016-05-22 first post
2016-05-23 new lib
2016-08-24 ignore scr
2016-08-24 kicad schema, done!
2016-08-25 added project kicad extension
2016-08-25 first pcb spread, and pdf
2016-10-14 working on Cenon silkscreen
2016-10-14 pdf 1.4
2016-10-14 testing svg import to cenn
2016-10-14 flaten:
2016-10-22 diy halfbridge plans from hasadna/x_Bisv612ek%5B1-25%5D
2016-10-22 diyshield
2016-10-22 added udis brake, think thats the latest design 19.03.15
2016-11-13 udi_hbridge_w_opamps.png added
2017-07-13 added cam from sparkfun, pcbway uses them

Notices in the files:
ATTAMI-V0.00.sch:
LICENSE: CERN OHL 1.7
parts and their libraries:
SparkFun-Passives: Licensing: Creative Commons ShareAlike 4.0 International - https://creativecommons.org/licenses/by-sa/4.0
microbuilder: This work is placed in the public domain, and may be freely used for commercial and non-commercial work with the following conditions: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
